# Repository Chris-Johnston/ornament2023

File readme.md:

# Xmas Ornament 2023

An ATTiny404 LED Xmas tree ornament.

This year I waited until the last minute,
[and so this design is very derivative of last year's design.](https://github.com/Chris-Johnston/ornament2022)

## Resources used

- [svg2mod] was used to generate the footprint of the board, and the front silkscreen layer
  - I licensed a stock image for the front layer silkscreen
- I referred to [SerialUPDI] again as reference for getting UPDI working (and used the same adapter board from last year, apparently I had swapped +5V and GND somehow!?)
- [megaTinyCore] was used with Arduino (via the vscode Arduino extension) to upload to the ATTiny404

[svg2mod]: https://github.com/svg2mod/svg2mod
[SerialUPDI]: https://teddywarner.org/Projects/SerialUPDI/
[megaTinyCore]: https://github.com/SpenceKonde/megaTinyCore

## Bill of Materials

| Reference | Description | Part No. | Price |
| --------- | ----------- | -------- | ----- |
| PCB | | | $0.53 (+ $0.80 shipping because I did this late) |
| C1 | 1 uf 1206 capacitor | CL31B105KAHNNNE | $0.0534 |
| D1 - D6 | 1206 Bidirectional Red/Green LED | XZMDKVG55W-4 | $1.10 (0.1835 ea.) |
| R1 - R6 | 1206 47 ohm resistor | WR12X470 JTL | $0.06 ($0.0112 ea.)
| SW1 | 6x6mm Pushbutton | Generic | $0.05 |
| SW2 | Slide Switch | JS102011SAQN | $0.65 |
| U1 | Attiny404 | Attiny404-SSN | $0.59 |
| B1 | CR2023 Battery Holder | BH-25C-1 | $0.0785 |

Unit cost w/o shipping: $3.11

## Changes from last year's version

In 2021 I made [snowflake-ornament] and [2022 I made a tree ornament.](https://github.com/Chris-Johnston/ornament2022) This year doesn't have
many changes, other than a different footprint and one less LED.

One less LED fits better with this board layout, and also means that
each common I/O between the left and right side can use PWM.
Despite this, I didn't actually have time to implement anything which
uses the PWM, I was finishing the code the same day I was supposed to drop these off.

Since this was so rushed, the board layout had a few quirks and features. All of the LEDs but ONE face the same orientation,
and the back isn't very symmetric.
For the most part it all worked though.

[snowflake-ornament]: https://github.com/Chris-Johnston/snowflake-ornament

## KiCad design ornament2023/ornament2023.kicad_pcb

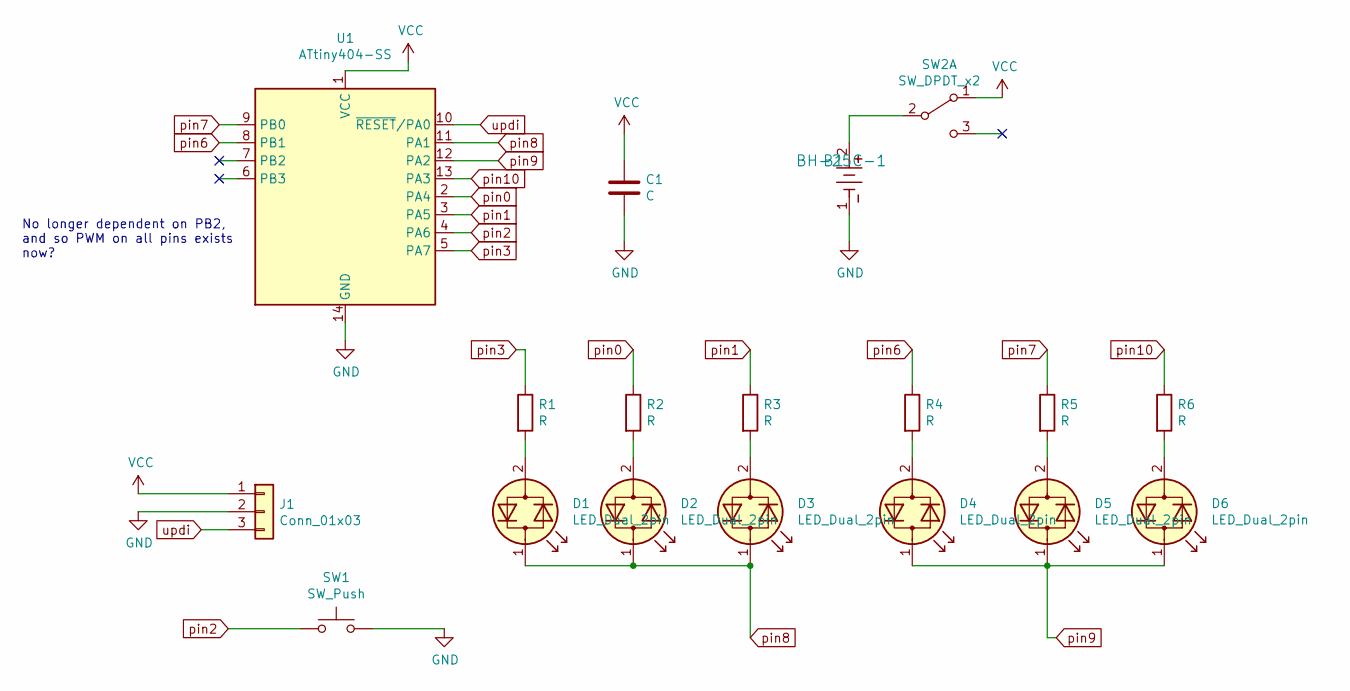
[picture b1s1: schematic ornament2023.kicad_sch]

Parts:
B1: BH-25C-1; BH-25C-1_ADM
C1: C; C_1206_3216Metric_Pad1.42x1.75mm_HandSolder
D1, D2, D3, D4, D5, D6: LED_Dual_2pin; Custom_LessSilkscreenLED_1206_3216Metric_Pad1.42x1.75mm_Han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
J1: Conn_01x03; custom_updipad_PinHeader_1x03_P2.54mm_Vertical
R1, R2, R3, R4, R5, R6: R; R_1206_3216Metric_Pad1.42x1.75mm_HandSolder
SW1: SW_Push; SW_Push_1P1T_NO_6x6mm_H9.5mm
SW2: SW_DPDT_x2; SW_SPDT_CK-JS102011SAQN
U1: ATtiny404-SS; SOIC-14_3.9x8.7mm_P1.27mm

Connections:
GND: B1.1, C1.2, J1.2, SW1.2, U1.14 (GND)
unnamed: D1.2 (AK), R1.2
unnamed: D2.2 (AK), R2.2
unnamed: D3.2 (AK), R3.2
unnamed: D4.2 (AK), R4.2
unnamed: D5.2 (AK), R5.2
unnamed: D6.2 (AK), R6.2
unnamed: B1.2, SW2.2 (B)
VCC: C1.1, J1.1, SW2.1 (A), U1.1 (VCC)
pin0: R2.1, U1.2 (PA4)
pin1: R3.1, U1.3 (PA5)
pin2: SW1.1, U1.4 (PA6)
pin3: R1.1, U1.5 (PA7)
pin6: R4.1, U1.8 (PB1)
pin7: R5.1, U1.9 (PB0)
pin8: D1.1 (KA), D2.1 (KA), D3.1 (KA), U1.11 (PA1)
pin9: D4.1 (KA), D5.1 (KA), D6.1 (KA), U1.12 (PA2)
pin10: R6.1, U1.13 (PA3)
updi: J1.3, U1.10 (~RESET/PA0)

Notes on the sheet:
No longer dependent on PB2, and so PWM on all pins exists now?

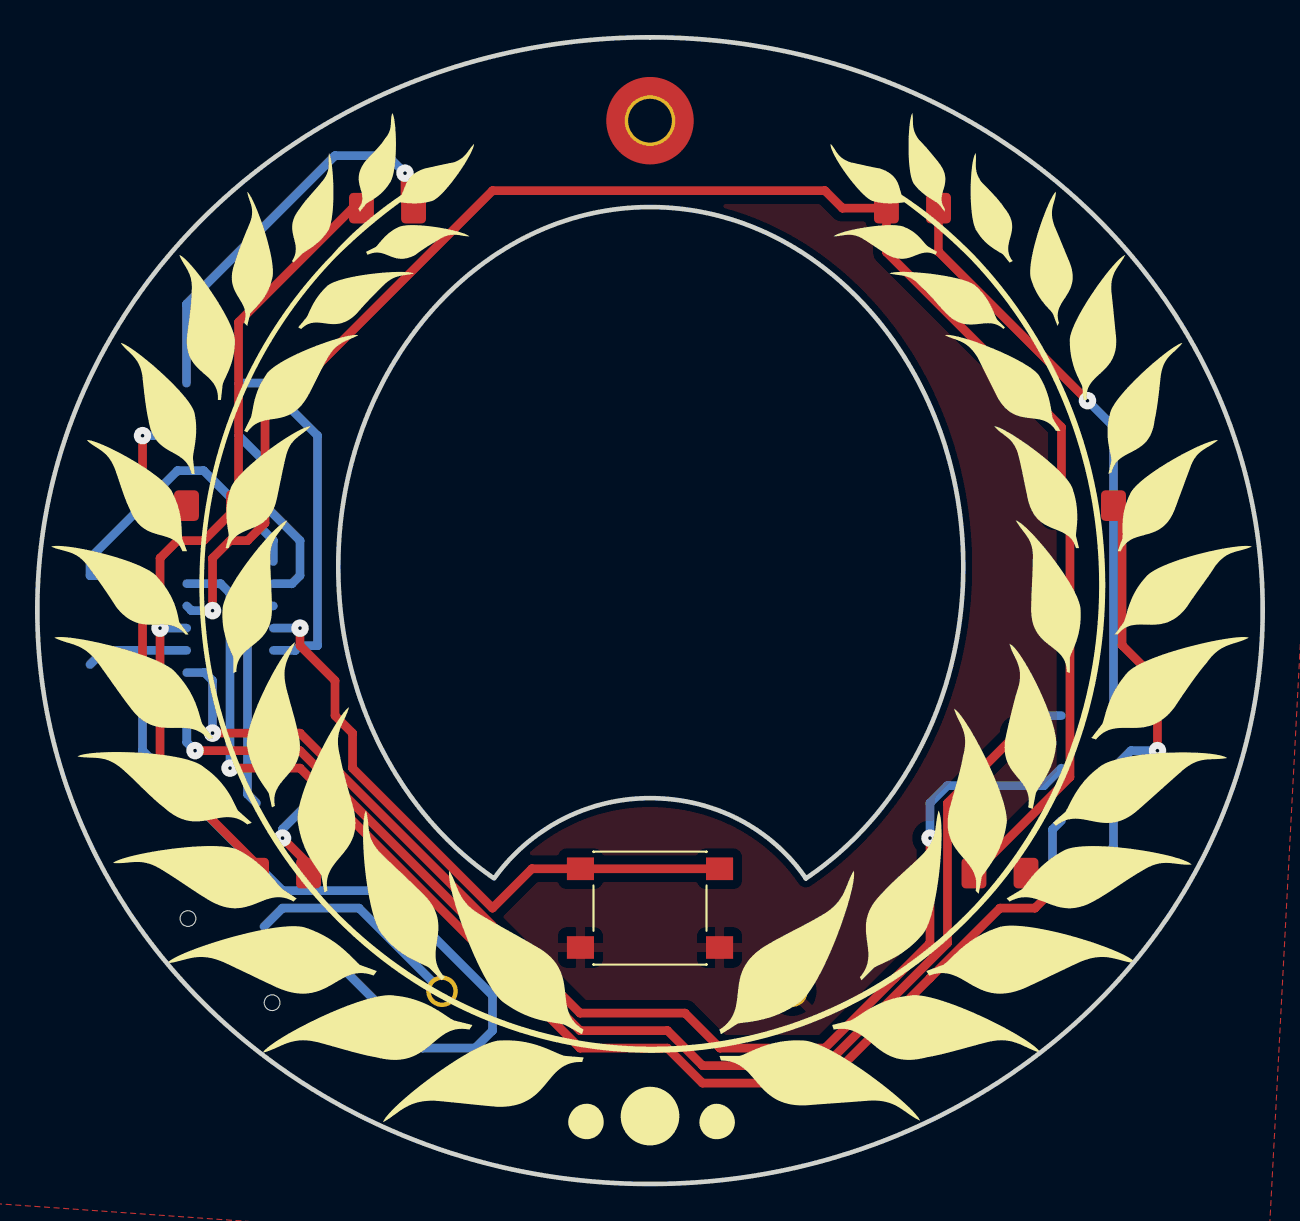
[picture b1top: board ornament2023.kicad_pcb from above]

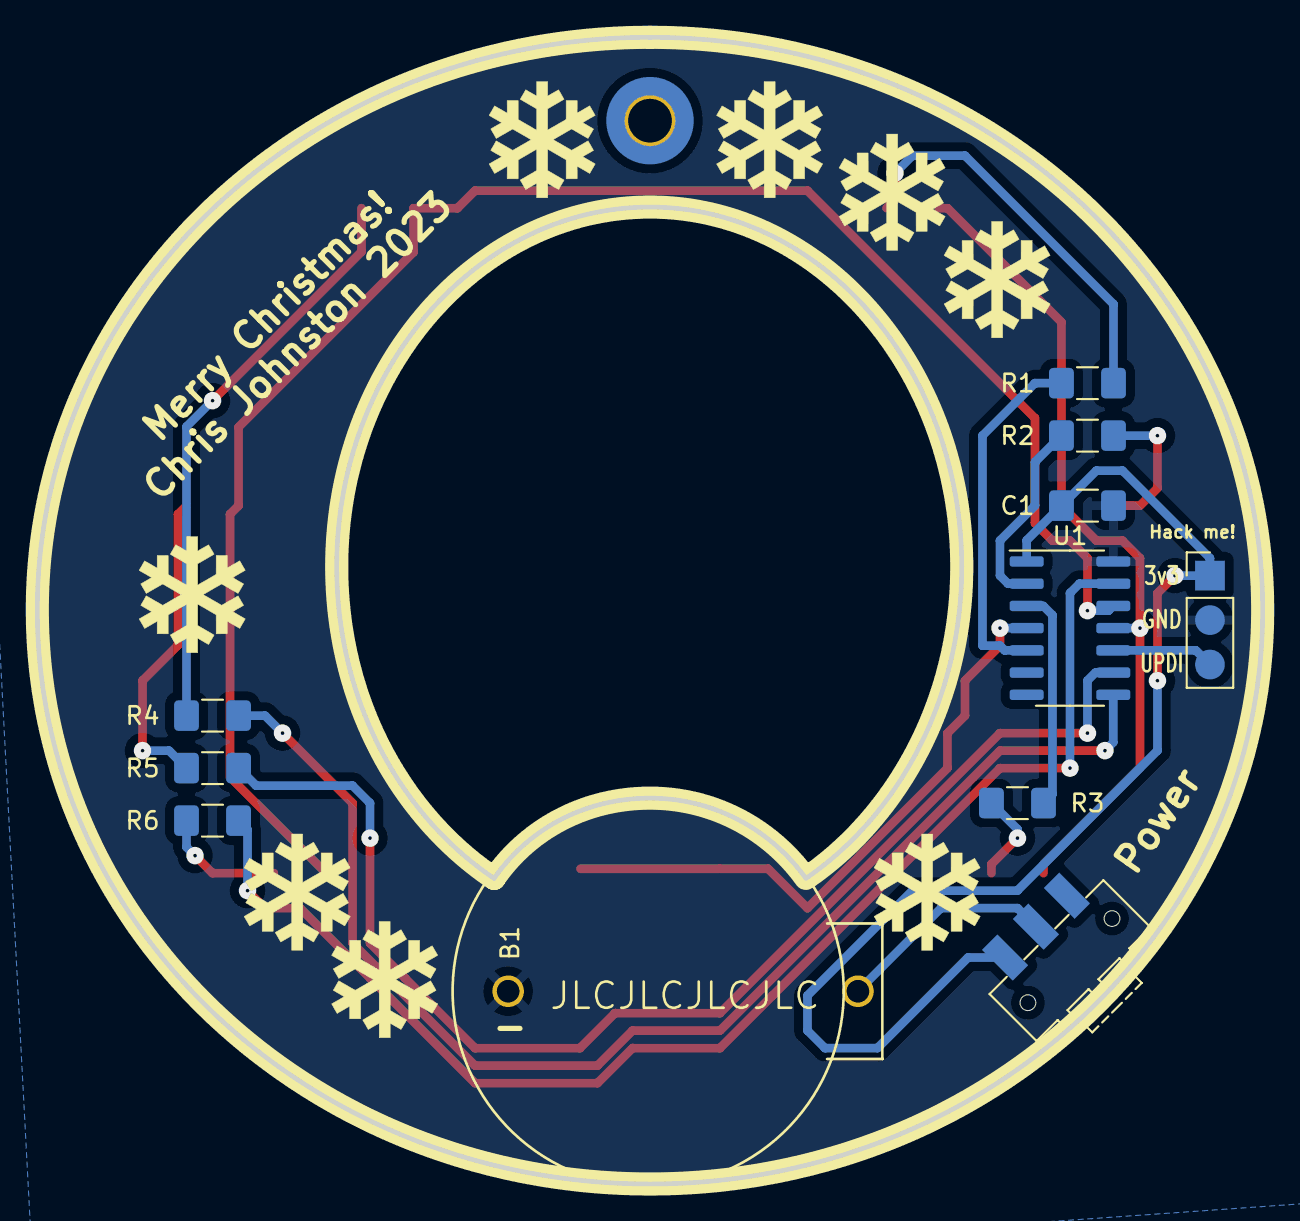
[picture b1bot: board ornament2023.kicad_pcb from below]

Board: 2 copper layers, 70.0 x 65.5 mm, 27 parts (19 on the bottom side), 19 nets.

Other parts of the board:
svg2mod: G***; wreath
svg2mod#2, svg2mod#3, svg2mod#4, svg2mod#5, svg2mod#6, svg2mod#7, svg2mod#8, svg2mod#9: G***; Snow_flake2

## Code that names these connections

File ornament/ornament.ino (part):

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int bottomColor = 0;

// pin with the button
int buttonIn = 2; // PA6
#define PIN_BUTTON 2
#define DEBOUNCE_TIME 150
#define NUM_PATTERNS 10
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{

// 3, 1, 0, 5
// PA7, PA5, PA4, PB2
// 6, 7, 10
// PB1, PB0, PA3
// 8, 9
// PA1, PA2

  // 7 5 4
  int topa_mask = 0b10110000;
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
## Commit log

2023-11-26 kinda just sat down and did this all in one go
2023-12-24 add ornament code copied from last year
2023-12-24 add arduino settings
2023-12-26 last-minute code changes
2023-12-26 documentation
